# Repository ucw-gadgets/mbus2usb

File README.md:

# USB to Mbus master board

Galvanically isolated USB to Mbus converter. Input voltage depends on external
step-up board, intended for use with cheap chinese step-up. USB communication
part is galvanically isolated.

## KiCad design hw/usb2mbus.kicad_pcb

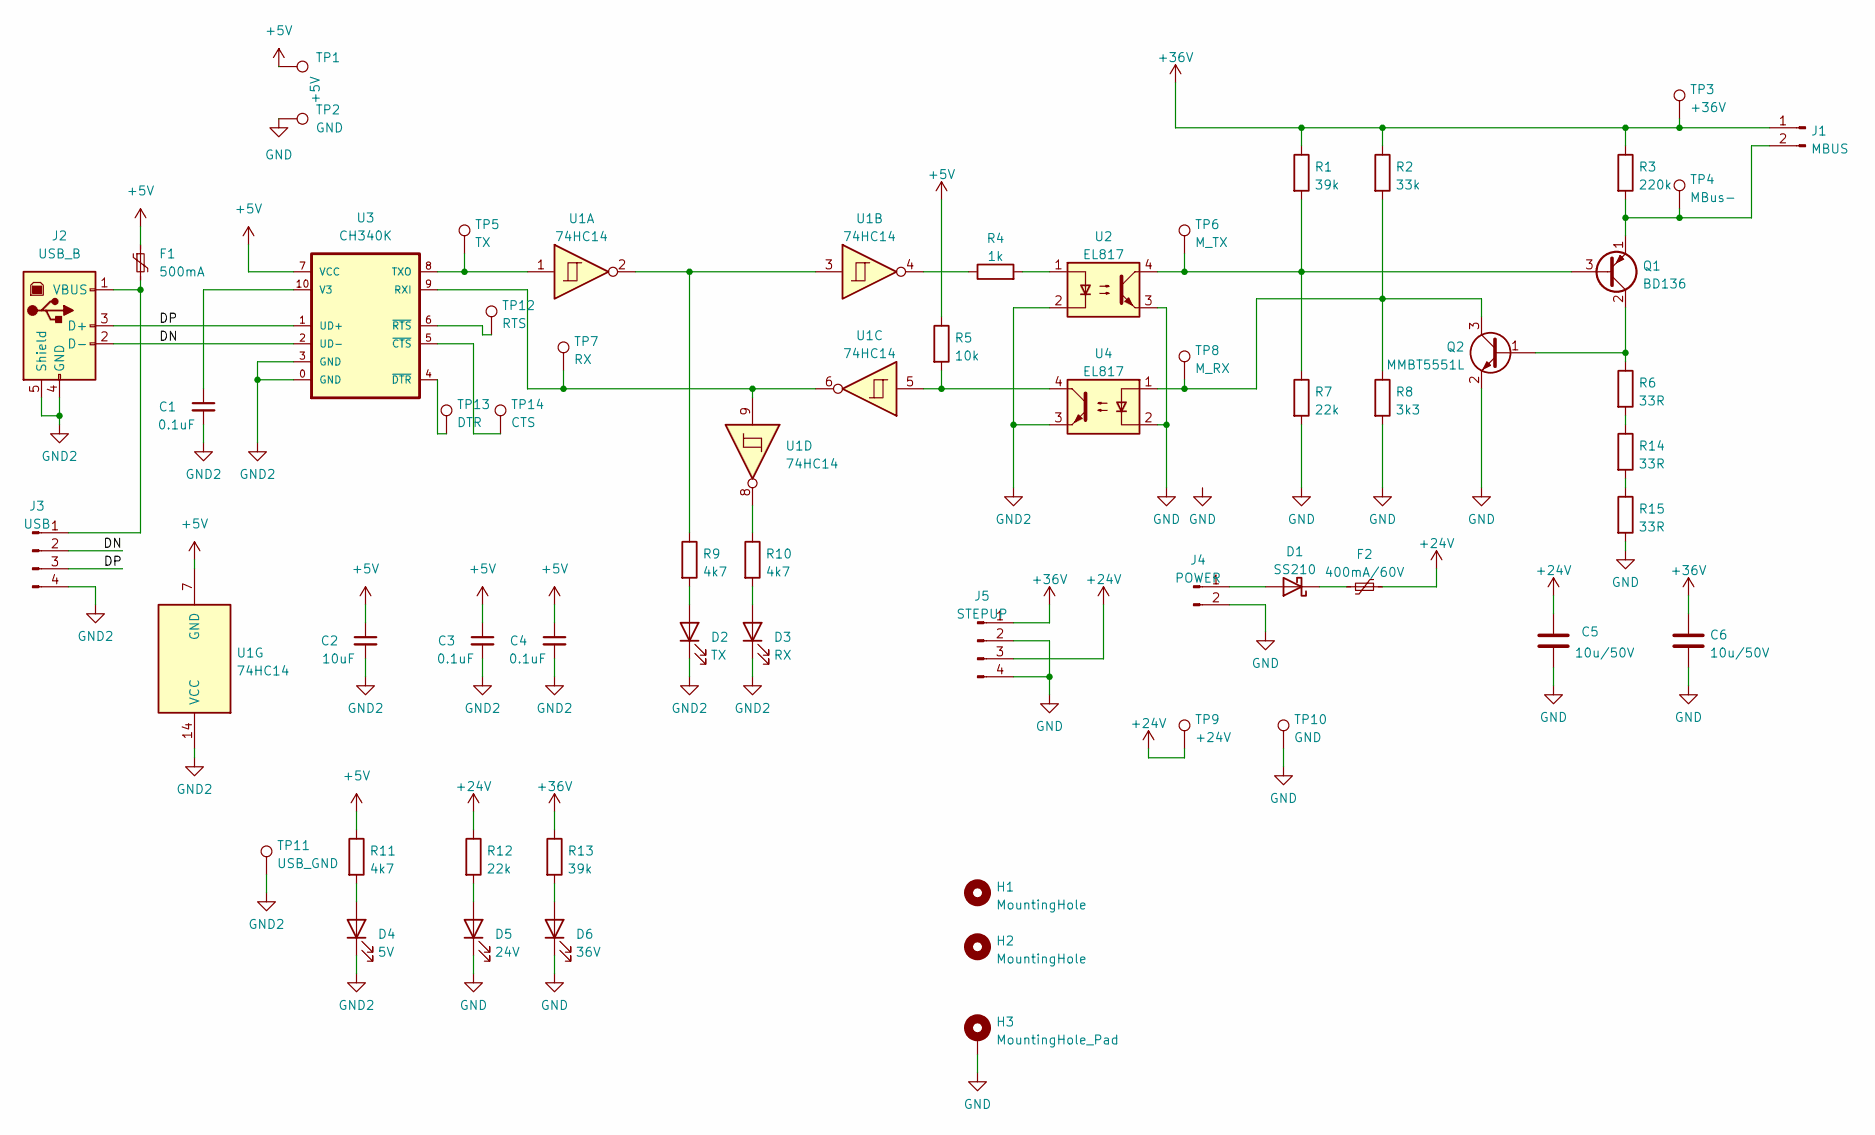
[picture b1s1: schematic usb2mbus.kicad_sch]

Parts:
C1, C3, C4: 0.1uF; C_0603_1608Metric; LCSC C14663
C2: 10uF; C_0603_1608Metric; LCSC C96446
C5: 10u/50V; LCSC C440198
C6: 10u/50V; C_0805_2012Metric; LCSC C440198
D1: D_Schottky; LCSC C14996
D2: TX; LCSC C2286
D3: RX; LED_0603_1608Metric; LCSC C2286
D4: 5V; LED_0603_1608Metric; LCSC C72043
D5: 24V; LED_0603_1608Metric; LCSC C72043
D6: 36V; LED_0603_1608Metric; LCSC C72043
F1: 500mA; Fuse_0603_1608Metric; LCSC C2844463
F2: Polyfuse_Small; LCSC C462518
H1: MountingHole
H2: MountingHole; MountingHole_3.2mm_M3_ISO14580
H3: MountingHole_Pad
J1: MBUS
J2: USB_B; USB_B_Lumberg_2411_02_Horizontal
J3: USB; PinHeader_1x04_P2.54mm_Vertical
J4: POWER
J5: STEPUP
Q1: BD136
Q2: MMBT5551L; LCSC C2145
R1: 39k; LCSC C23153
R2: 33k; R_0603_1608Metric; LCSC C4216
R3: 220k; R_0603_1608Metric; LCSC C22961
R4: 1k; LCSC C21190
R5: 10k; R_0603_1608Metric; LCSC C25804
R6, R14, R15: 33R; R_0805_2012Metric; LCSC C17634
R7, R12: 22k; R_0603_1608Metric; LCSC C31850
R8: 3k3; R_0603_1608Metric; LCSC C22978
R9, R11: 4k7; R_0603_1608Metric; LCSC C23162
R10: 4k7; LCSC C23162
R13: 39k; R_0603_1608Metric; LCSC C23153
TP1: +5V; TestPoint_THTPad_D2.0mm_Drill1.0mm
TP2, TP10: GND; TestPoint_THTPad_D2.0mm_Drill1.0mm
TP3: +36V; TestPoint_THTPad_D2.0mm_Drill1.0mm
TP4: MBus-; TestPoint_THTPad_D2.0mm_Drill1.0mm
TP5: TX; TestPoint_THTPad_D2.0mm_Drill1.0mm
TP6: M_TX; TestPoint_THTPad_D2.0mm_Drill1.0mm
TP7: RX
TP8: M_RX; TestPoint_THTPad_D2.0mm_Drill1.0mm
TP9: +24V; TestPoint_THTPad_D2.0mm_Drill1.0mm
TP11: USB_GND; TestPoint_THTPad_D2.0mm_Drill1.0mm
TP12: RTS; TestPoint_THTPad_D2.0mm_Drill1.0mm
TP13: DTR; TestPoint_THTPad_D2.0mm_Drill1.0mm
TP14: CTS; TestPoint_THTPad_D2.0mm_Drill1.0mm
U1: 74HC14; LCSC C5605
U2: EL817; LCSC C106900
U3: CH340K; SSOP-10_3.9x4.9mm_P1.00mm; LCSC C968586
U4: EL817; SMDIP-4_W7.62mm; LCSC C106900

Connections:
+5V: C2.1, C3.1, C4.1, F1.1, R5.1, R11.1, TP1.1, U1.7 (GND), U3.7 (VCC)
+24V: C5.1, F2.2, J5.3, R12.1, TP9.1
+36V: C6.1, J1.1, J5.1, R1.1, R2.1, R3.1, R13.1, TP3.1
/DN: J2.2 (D-), J3.2, U3.2 (UD-)
/DP: J2.3 (D+), J3.3, U3.1 (UD+)
GND: C5.2, C6.2, D5.1 (K), D6.1 (K), H3.1, J4.2, J5.2, J5.4, Q2.2 (E), R7.2, R8.2, R15.2, TP2.1, TP10.1, U2.3, U4.2
GND2: C1.2, C2.2, C3.2, C4.2, D2.1 (K), D3.1 (K), D4.1 (K), J2.4 (GND), J2.5 (Shield), J3.4, TP11.1, U1.14 (VCC), U2.2, U3.0 (GND), U3.3 (GND), U4.3
unnamed: C1.1, U3.10 (V3)
unnamed: D1.1 (K), F2.1
unnamed: D1.2 (A), J4.1
unnamed: D2.2 (A), R9.2
unnamed: D3.2 (A), R10.2
unnamed: D4.2 (A), R11.2
unnamed: D5.2 (A), R12.2
unnamed: D6.2 (A), R13.2
unnamed: F1.2, J2.1 (VBUS), J3.1
unnamed: J1.2, Q1.1 (E), R3.2, TP4.1
unnamed: Q1.2 (C), Q2.1 (B), R6.1
unnamed: Q1.3 (B), R1.2, R7.1, TP6.1, U2.4
unnamed: Q2.3 (C), R2.2, R8.1, TP8.1, U4.1
unnamed: R4.1, U1.4
unnamed: R4.2, U2.1
unnamed: R5.2, U1.5, U4.4
unnamed: R6.2, R14.1
unnamed: R9.1, U1.2, U1.3
unnamed: R10.1, U1.8
unnamed: R14.2, R15.1
unnamed: TP5.1, U1.1, U3.8 (TXO)
unnamed: TP7.1, U1.6, U1.9, U3.9 (RXI)
unnamed: TP13.1, U3.4 (~DTR)
unnamed: TP14.1, U3.5 (~CTS)
unnamed: TP12.1, U3.6 (~RTS)

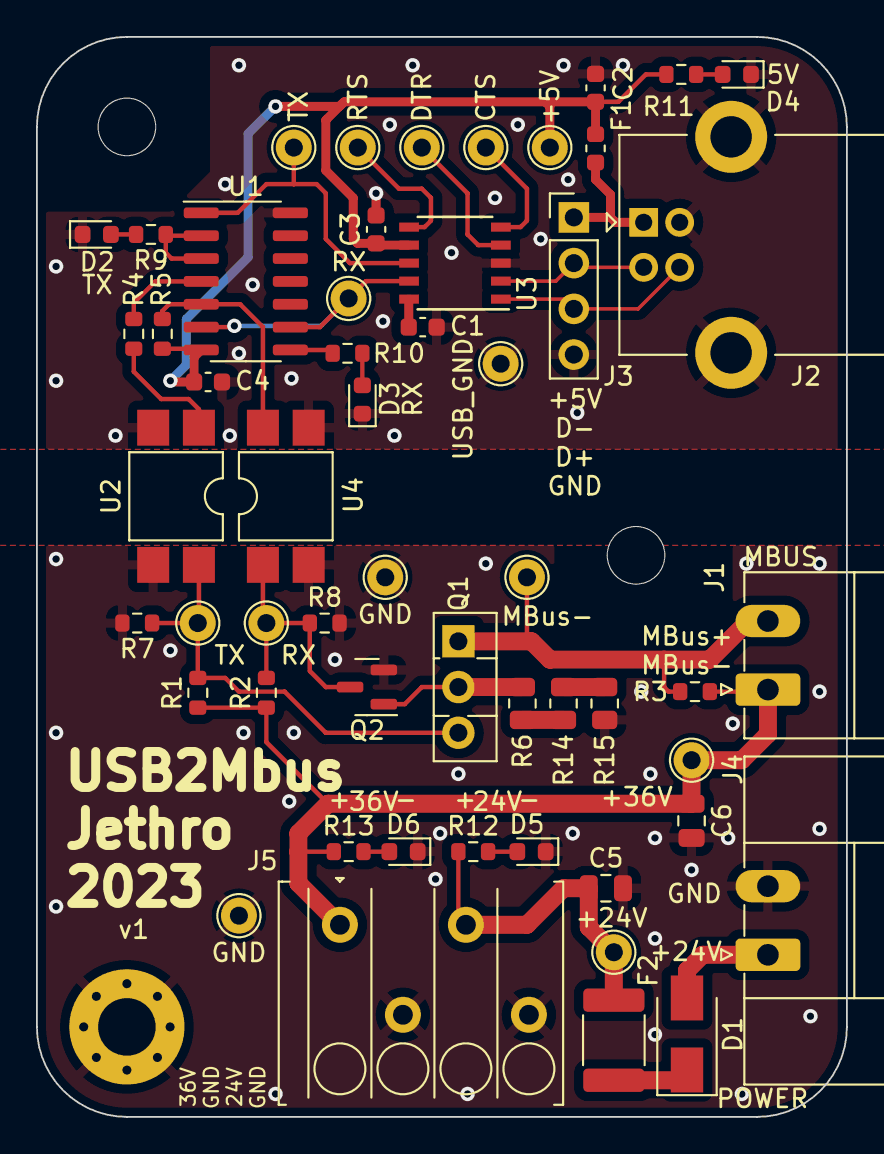
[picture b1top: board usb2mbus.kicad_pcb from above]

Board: 2 copper layers, 45.0 x 60.0 mm, 57 parts (0 on the bottom side), 32 nets.

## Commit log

2023-01-28 First version of the hardware.
2023-01-28 Better README
